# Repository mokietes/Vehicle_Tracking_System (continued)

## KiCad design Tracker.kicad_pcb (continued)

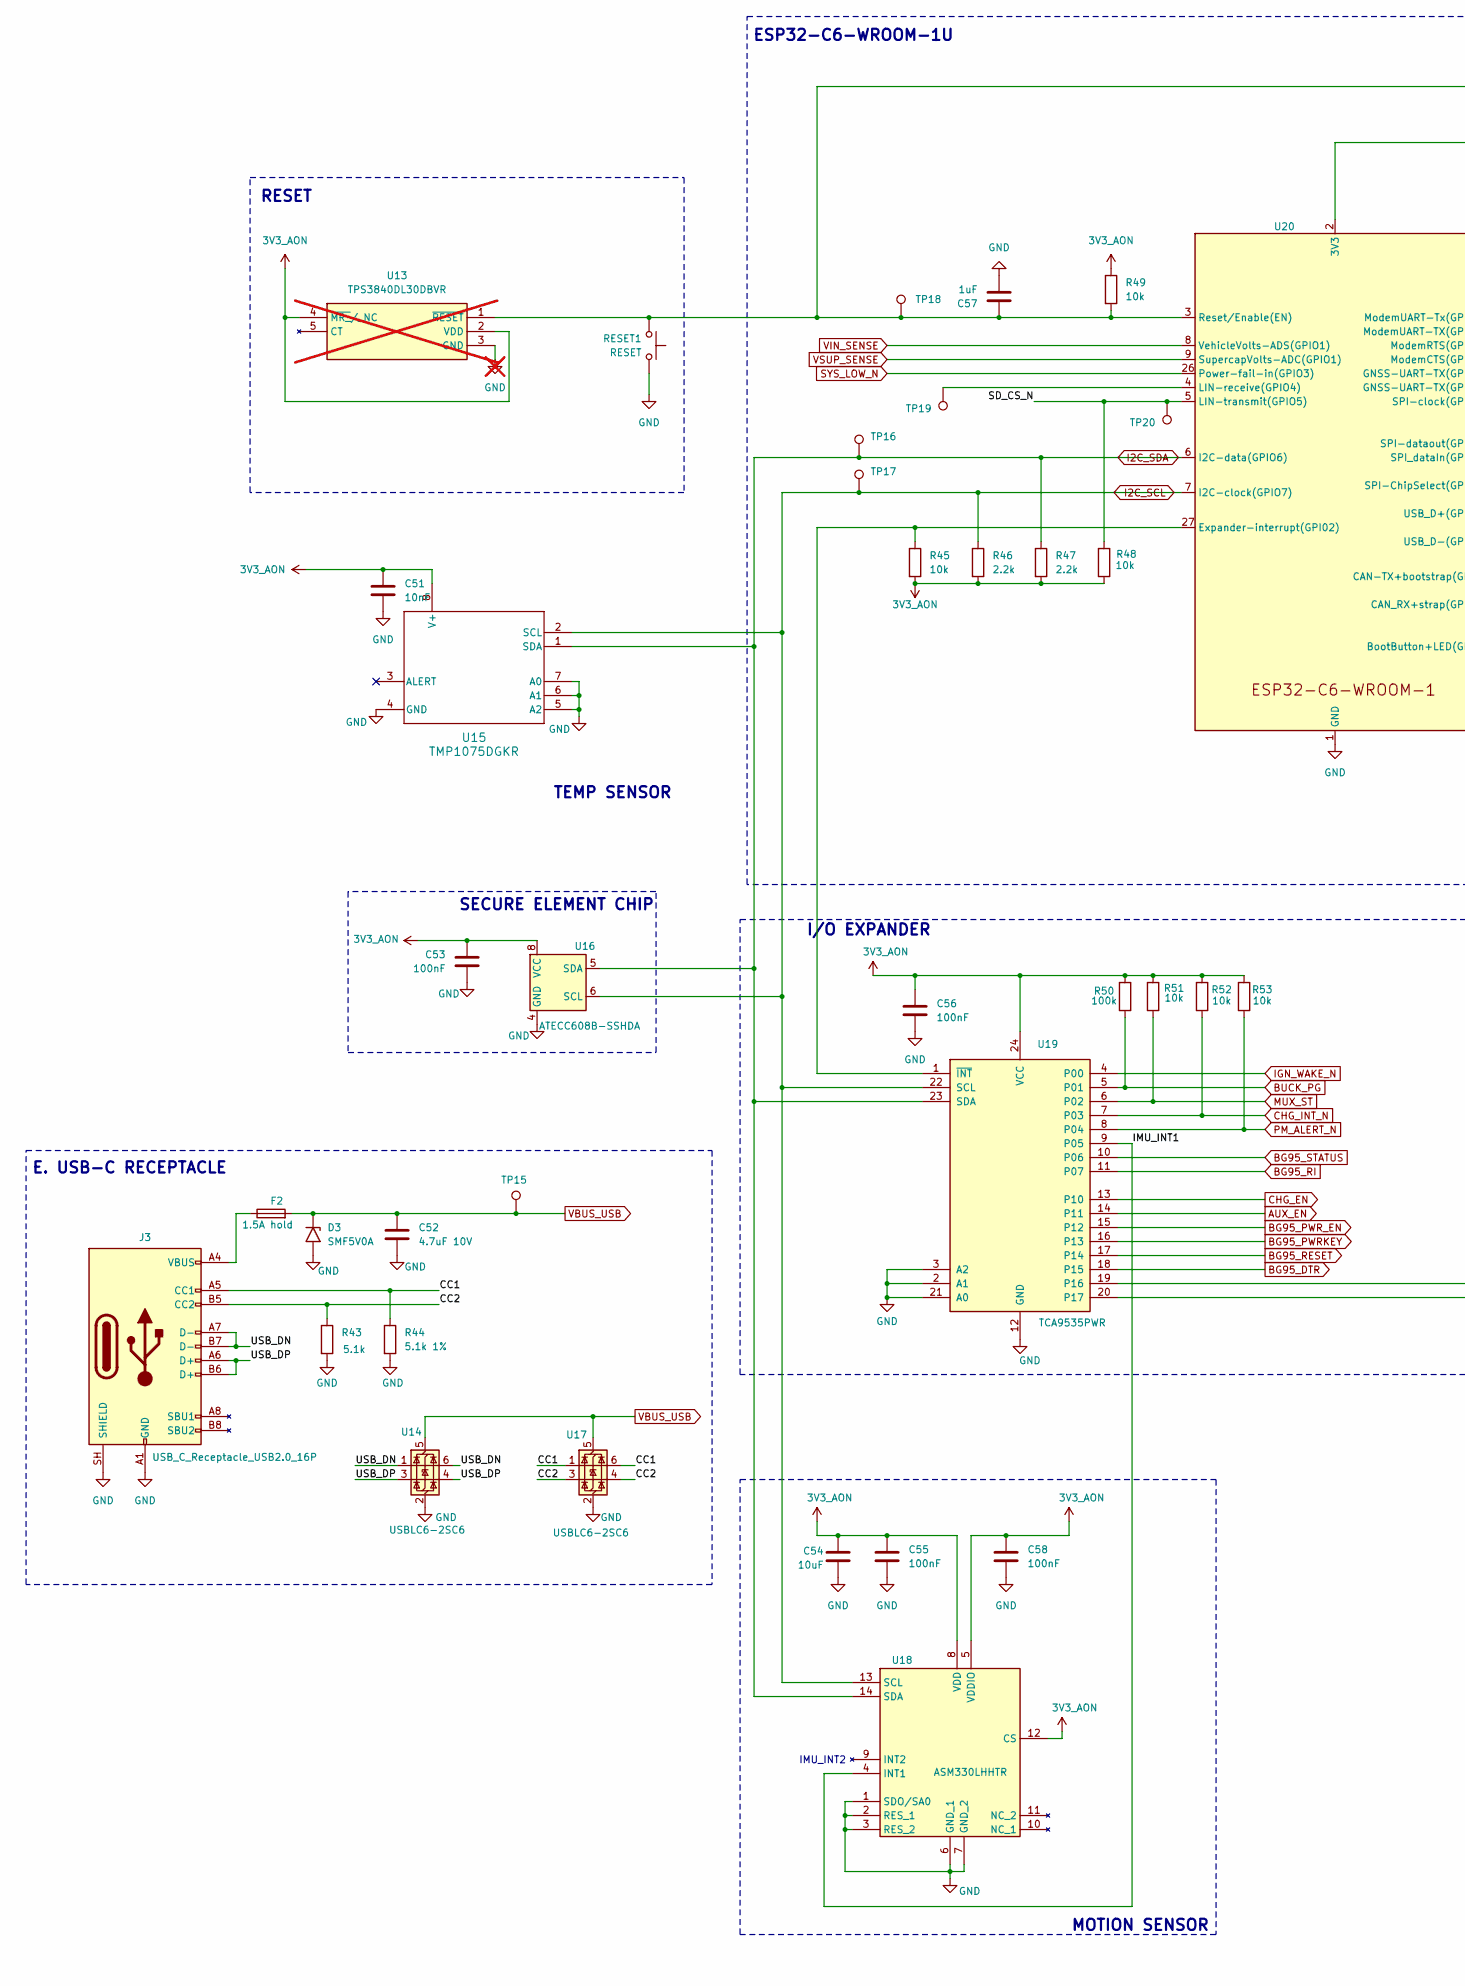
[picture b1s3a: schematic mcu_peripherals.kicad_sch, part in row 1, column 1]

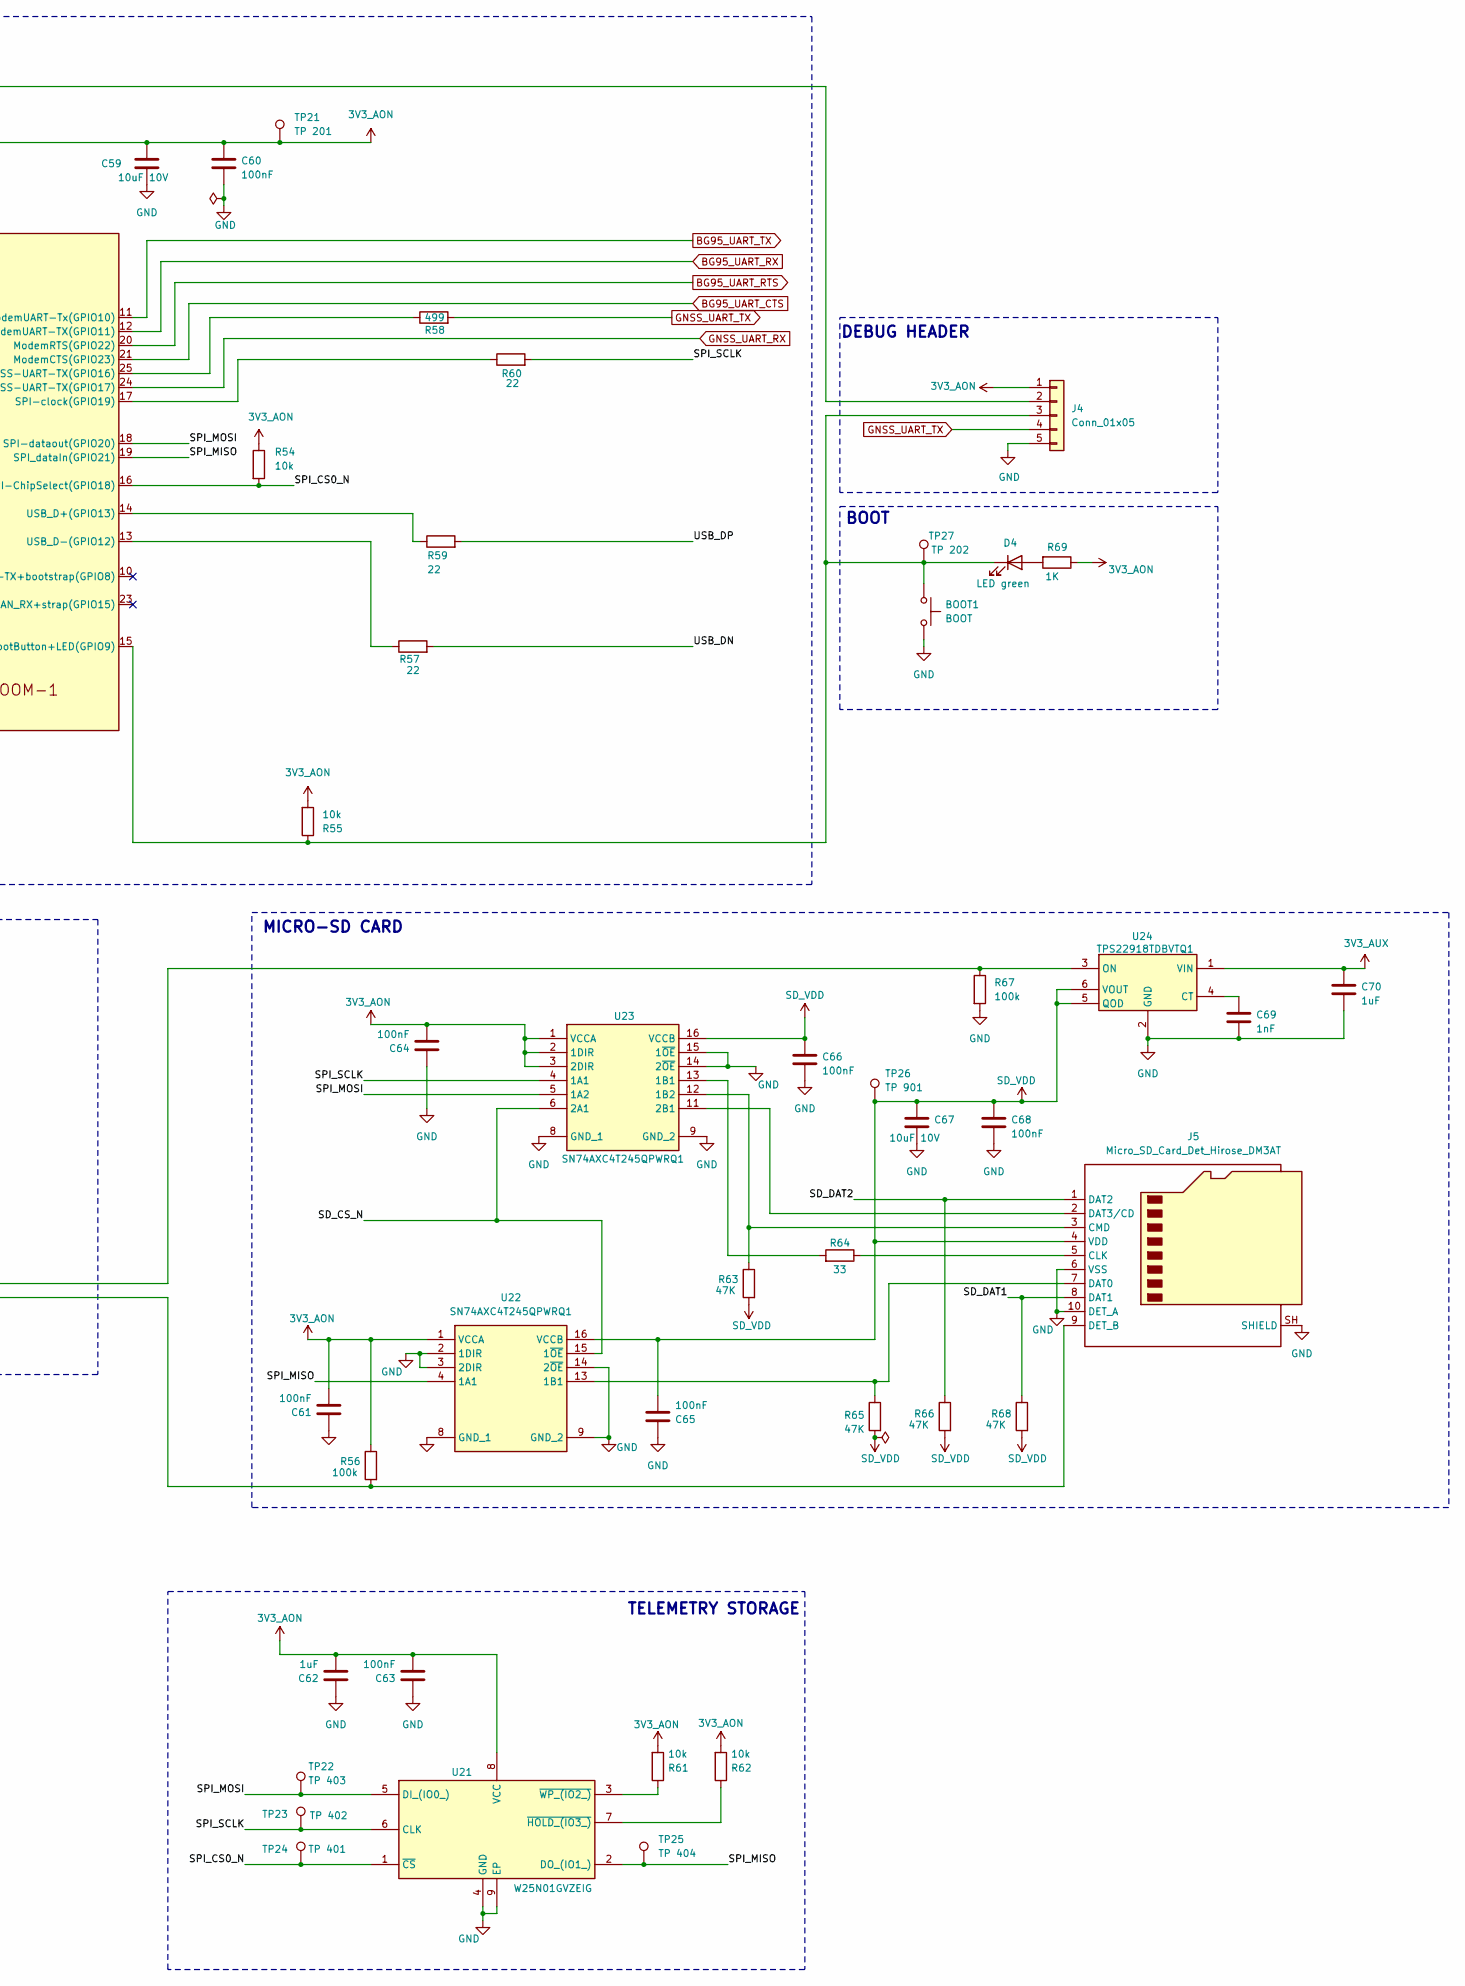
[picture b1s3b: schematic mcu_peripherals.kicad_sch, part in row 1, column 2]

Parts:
BOOT1: BOOT; SW_SPST_TL3342
C51: 10nF; C_0603_1608Metric
C52: 4.7uF 10V; C_0805_2012Metric
C53, C55, C56, C58, C60, C61, C63, C64, C65, C66, C68: 100nF; C_0402_1005Metric
C54: 10uF; C_0402_1005Metric
C57: 1uF; C_0603_1608Metric
C59, C67: 10uF 10V; C_0805_2012Metric
C62, C70: 1uF; C_0402_1005Metric
C69: 1nF; C_0402_1005Metric
D3: SMF5V0A; D_SMF
D4: LED green; LED_0603_1608Metric
F2: 1.5A hold; Fuse_1206_3216Metric
J3: USB_C_Receptacle_USB2.0_16P; USB_C_Receptacle_GCT_USB4105-xx-A_16P_TopMnt_Horizontal
J4: Conn_01x05; PinSocket_1x05_P2.54mm_Vertical
J5: Micro_SD_Card_Det_Hirose_DM3AT; microSD_HC_Hirose_DM3AT-SF-PEJM5
R43: 5.1k; R_1206_3216Metric
R44: 5.1k 1%; R_1206_3216Metric
R45, R49, R51, R52, R53, R54, R55: 10k; R_0603_1608Metric
R46, R47: 2.2k; R_0603_1608Metric
R48, R61, R62: 10k; R_0402_1005Metric
R50: 100k; R_0603_1608Metric
R56, R67: 100k; R_0402_1005Metric
R57, R59, R60: 22; R_0603_1608Metric
R58: 499; R_0603_1608Metric
R63, R65, R66, R68: 47K; R_0402_1005Metric
R64: 33; R_0402_1005Metric
R69: 1K; R_0603_1608Metric
RESET1: RESET; SW_SPST_TL3342
TP15: TestPoint_Pad_D1.5mm
TP16, TP17, TP18, TP19, TP20: TestPoint; TestPoint_Pad_D1.5mm
TP21: TP 201; TestPoint_Pad_D1.5mm
TP22: TP 403; TestPoint_Pad_D1.5mm
TP23: TP 402; TestPoint_Pad_D1.5mm
TP24: TP 401; TestPoint_Pad_D1.5mm
TP25: TP 404; TestPoint_Pad_D1.5mm
TP26: TP 901; TestPoint_Pad_D1.5mm
TP27: TP 202; TestPoint_Pad_D1.5mm
U13: TPS3840DL30DBVR; SOT95P280X145-5N; Manufacturer_Part_Number TPS3840DL30DBVR; Mouser Part Number 595-TPS3840DL30DBVR; not fitted
U14, U17: USBLC6-2SC6; SOT-23-6
U15: TMP1075DGKR; VSSOP-8_3x3mm_P0.65mm
U16: ATECC608B-SSHDA; SOIC-8_3.9x4.9mm_P1.27mm
U18: ASM330LHHTR; LSM6DS3USTR; Manufacturer_Part_Number ASM330LHHTR; Mouser Part Number 511-ASM330LHHTR
U19: TCA9535PWR; TSSOP-24_4.4x7.8mm_P0.65mm
U20: ESP32-C6-WROOM-1
U21: W25N01GVZEIG; SON127P800X600X80-9N-D; Manufacturer_Part_Number W25N01GVZEIG; Mouser Part Number 454-W25N01GVZEIG
U22, U23: SN74AXC4T245QPWRQ1; SOP65P640X120-16N; Manufacturer_Part_Number SN74AXC4T245QPWRQ1; Mouser Part Number 595-74AXC4T245QPWRQ1
U24: TPS22918TDBVTQ1; SOT95P280X145-6N; Manufacturer_Part_Number TPS22918TDBVTQ1; Mouser Part Number 595-TPS22918TDBVTQ1

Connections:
3V3_AON: C51.1, C53.1, C54.1, C55.1, C56.1, C58.1, C59.1, C60.1, C61.2, C62.2, C63.2, C64.2, J4.1, R45.2, R46.2, R47.2, R48.1, R49.1, R50.2, R51.2, R52.2, R53.2, R54.1, R55.2, R56.1, R61.2, R62.2, R69.1, TP21.1 (1_1), U13.2 (VDD), U13.4 (~MR_/_NC), U15.8 (V+), U16.8 (VCC), U18.5 (VDDIO), U18.8 (VDD), U18.12 (CS), U19.24 (VCC), U20.2 (3V3), U21.8 (VCC), U22.1 (VCCA), U23.1 (VCCA), U23.2 (1DIR), U23.3 (2DIR); also elsewhere on the board
3V3_AUX: C70.1, U24.1 (VIN); also elsewhere on the board
/MCU_PERIPHERALS/CC1: J3.A5 (CC1), R44.1, U17.1 (I/O1), U17.6 (I/O1)
/MCU_PERIPHERALS/CC2: J3.B5 (CC2), R43.1, U17.3 (I/O2), U17.4 (I/O2)
/MCU_PERIPHERALS/IMU_INT1: U18.4 (INT1), U19.9 (P05)
/MCU_PERIPHERALS/SD_CS_N: R48.2, TP20.1 (1_1), U20.5 (LIN-transmit(GPIO5)), U22.15 (1~OE), U23.6 (2A1)
/MCU_PERIPHERALS/SD_DAT1: J5.8 (DAT1), R68.1
/MCU_PERIPHERALS/SD_DAT2: J5.1 (DAT2), R66.1
/MCU_PERIPHERALS/SPI_CS0_N: R54.2, TP24.1 (1_1), U20.16 (SPI-ChipSelect(GPIO18)), U21.1 (~CS)
/MCU_PERIPHERALS/SPI_MISO: TP25.1 (1_1), U20.19 (SPI_dataIn(GPIO21)), U21.2 (DO_(IO1_)), U22.4 (1A1)
/MCU_PERIPHERALS/SPI_MOSI: TP22.1 (1_1), U20.18 (SPI-dataout(GPIO20)), U21.5 (DI_(IO0_)), U23.5 (1A2)
/MCU_PERIPHERALS/SPI_SCLK: R60.2, TP23.1 (1_1), U21.6 (CLK), U23.4 (1A1)
/MCU_PERIPHERALS/USB_DN: J3.A7 (D-), J3.B7 (D-), R57.2, U14.1 (I/O1), U14.6 (I/O1)
/MCU_PERIPHERALS/USB_DP: J3.A6 (D+), J3.B6 (D+), R59.2, U14.3 (I/O2), U14.4 (I/O2)
AUX_EN: U19.14 (P11); also elsewhere on the board
BG95_DTR: U19.18 (P15); also elsewhere on the board
BG95_PWRKEY: U19.16 (P13); also elsewhere on the board
BG95_PWR_EN: U19.15 (P12); also elsewhere on the board
BG95_RESET: U19.17 (P14); also elsewhere on the board
BG95_RI: U19.11 (P07); also elsewhere on the board
BG95_STATUS: U19.10 (P06); also elsewhere on the board
BG95_UART_CTS: U20.21 (ModemCTS(GPIO23)); also elsewhere on the board
BG95_UART_RTS: U20.20 (ModemRTS(GPIO22)); also elsewhere on the board
BG95_UART_RX: U20.12 (ModemUART-TX(GPIO11)); also elsewhere on the board
BG95_UART_TX: U20.11 (ModemUART-Tx(GPIO10)); also elsewhere on the board
BUCK_PG: R50.1, U19.5 (P01); also elsewhere on the board
CHG_EN: U19.13 (P10); also elsewhere on the board
CHG_INT_N: R52.1, U19.7 (P03); also elsewhere on the board
GND: BOOT1.2, C51.2, C52.2, C53.2, C54.2, C55.2, C56.2, C57.2, C58.2, C59.2, C60.2, C61.1, C62.1, C63.1, C64.1, C65.1, C66.2, C67.2, C68.2, C69.2, C70.2, D3.2 (A2), J3.A1 (GND), J3.A12 (GND), J3.B1 (GND), J3.B12 (GND), J3.SH (SHIELD), J4.5, J5.6 (VSS), J5.10 (DET_A), J5.SH (SHIELD), R43.2, R44.2, R67.2, RESET1.1, U13.3 (GND), U14.2 (GND), U15.4 (GND), U15.5 (A2), U15.6 (A1), U15.7 (A0), U16.4 (GND), U17.2 (GND), U18.1 (SDO/SA0), U18.2 (RES_1), U18.3 (RES_2), U18.6 (GND_1), U18.7 (GND_2), U19.2 (A1), U19.3 (A2), U19.12 (GND), U19.21 (A0), U20.1 (GND), U20.28 (GND), U20.29 (GND), U21.4 (GND), U21.9 (EP), U22.2 (1DIR), U22.3 (2DIR), U22.8 (GND_1), U22.9 (GND_2), U22.14 (2~OE), U23.8 (GND_1), U23.9 (GND_2), U23.14 (2~OE), U23.15 (1~OE), U24.2 (GND); also elsewhere on the board
GNSS_UART_RX: U20.24 (GNSS-UART-TX(GPIO17)); also elsewhere on the board
GNSS_UART_TX: J4.4, R58.2; also elsewhere on the board
I2C_SCL: R46.1, TP17.1 (1_1), U15.2 (SCL), U16.6 (SCL), U18.13 (SCL), U19.22 (SCL), U20.7 (I2C-clock(GPIO7)); also elsewhere on the board
I2C_SDA: R47.1, TP16.1 (1_1), U15.1 (SDA), U16.5 (SDA), U18.14 (SDA), U19.23 (SDA), U20.6 (I2C-data(GPIO6)); also elsewhere on the board
IGN_WAKE_N: U19.4 (P00); also elsewhere on the board
MUX_ST: R51.1, U19.6 (P02); also elsewhere on the board
unnamed: D4.2 (A), R69.2
unnamed: BOOT1.1, D4.1 (K), J4.3, R55.1, TP27.1 (1_1), U20.15 (BootButton+LED(GPIO9))
unnamed: F2.1, J3.A4 (VBUS), J3.A9 (VBUS), J3.B4 (VBUS), J3.B9 (VBUS)
unnamed: C57.1, J4.2, R49.2, RESET1.2, TP18.1 (1_1), U13.1 (~RESET), U20.3 (Reset/Enable(EN))
unnamed: J5.5 (CLK), R64.1
unnamed: J5.3 (CMD), R63.1, U23.12 (1B2)
unnamed: J5.7 (DAT0), R65.1, U22.13 (1B1)
unnamed: J5.2 (DAT3/CD), U23.11 (2B1)
unnamed: J5.9 (DET_B), R56.2, U19.20 (P17)
unnamed: R67.1, U19.19 (P16), U24.3 (ON)
unnamed: R45.1, U19.1 (~INT), U20.27 (Expander-interrupt(GPI02))
unnamed: R58.1, U20.25 (GNSS-UART-TX(GPIO16))
unnamed: TP19.1 (1_1), U20.4 (LIN-receive(GPIO4))
unnamed: R60.1, U20.17 (SPI-clock(GPIO19))
unnamed: R59.1, U20.14 (USB_D+(GPIO13))
unnamed: R57.1, U20.13 (USB_D-(GPIO12))
unnamed: R62.1, U21.7 (~HOLD_(IO3_))
unnamed: R61.1, U21.3 (~WP_(IO2_))
unnamed: R64.2, U23.13 (1B1)
unnamed: C69.1, U24.4 (CT)
PM_ALERT_N: R53.1, U19.8 (P04); also elsewhere on the board
SD_VDD: C65.2, C66.1, C67.1, C68.1, J5.4 (VDD), R63.2, R65.2, R66.2, R68.2, TP26.1 (1_1), U22.16 (VCCB), U23.16 (VCCB), U24.5 (QOD), U24.6 (VOUT)
SYS_LOW_N: U20.26 (Power-fail-in(GPIO3)); also elsewhere on the board
VBUS_USB: C52.1, D3.1 (A1), F2.2, TP15.1 (1_1), U14.5 (VBUS), U17.5 (VBUS); also elsewhere on the board
VIN_SENSE: U20.8 (VehicleVolts-ADS(GPIO1)); also elsewhere on the board
VSUP_SENSE: U20.9 (SupercapVolts-ADC(GPIO1)); also elsewhere on the board

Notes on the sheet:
MOTION SENSOR
RESET
ESP32-C6-WROOM-1U
I/O EXPANDER
DEBUG HEADER
BOOT
TEMP SENSOR
MICRO-SD CARD
IMU_INT2
SECURE ELEMENT CHIP
E. USB-C RECEPTACLE
TELEMETRY STORAGE

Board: 4 copper layers, 278 parts (93 on the bottom side), 155 nets, no tracks yet.
